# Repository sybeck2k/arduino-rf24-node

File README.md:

# Arduino RF24 Node

@todo

# Credits
Original work credits [@maniacbug][1]

# License

[CC BY-NC-SA][2]

  [1]: http://maniacbug.wordpress.com/
  [2]: http://creativecommons.org/licenses/by-nc-sa/3.0/

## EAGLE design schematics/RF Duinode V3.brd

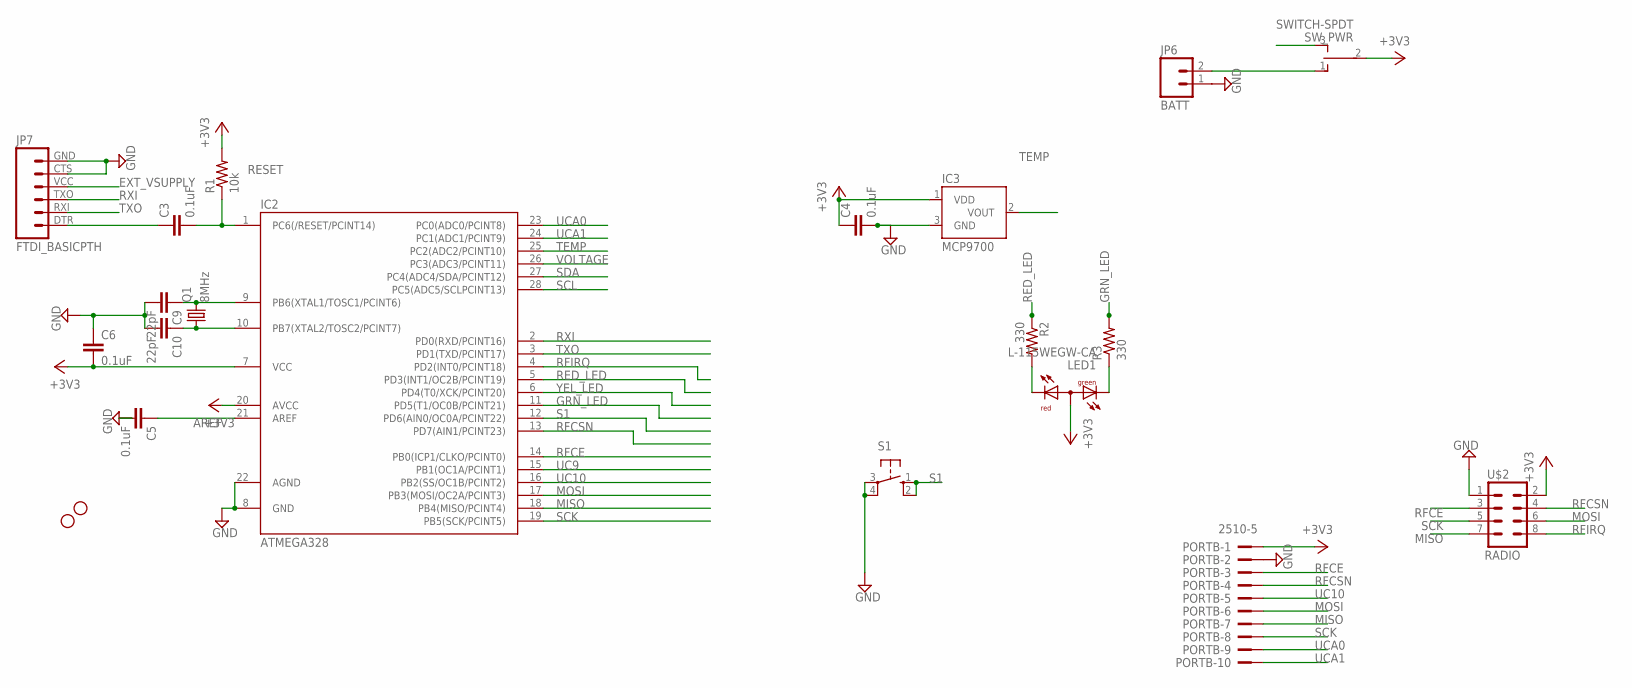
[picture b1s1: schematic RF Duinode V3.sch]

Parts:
C3, C4, C5, C6: 0.1uF; C025-025X050
C9, C10: 22pF; C025-025X050
IC2: ATMEGA328; DIL28-3
IC3: MCP9700; TO-92
JP2, JP8: STAND-OFF
JP6: BATT; 1X02_LOCK
JP7: FTDI_BASICPTH; FTDI_BASIC
LED1: L-115WEGW-CA; DUOLED-A-3MM
PORTB: 2510-5; PAK100/2500-5-10
Q1: 8MHz; HC49/S
R1: 10k; 0204V
R2, R3: 330; 0204V
S1: 10-XX; B3F-10XX
SW_PWR: SWITCH-SPDT; OS102011MS2QN1
U$2: RADIO; 2X4

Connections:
+3V3: C4.1, C6.2, IC2.7 (VCC), IC2.20 (AVCC), IC3.1 (VDD), LED1.2 (A), PORTB.1, R1.2, SW_PWR.2, U$2.2
AREF: C5.1, IC2.21 (AREF)
BATT: JP6.2, SW_PWR.1 (O)
DTR: C3.1, JP7.DTR (1)
EXT_VSUPPLY: JP7.VCC (4), SW_PWR.3 (S)
GND: C4.2, C5.2, C6.1, C9.2, C10.2, IC2.8 (GND), IC2.22 (AGND), IC3.3 (GND), JP6.1, JP7.CTS (5), JP7.GND (6), PORTB.2, S1.3, S1.4 (P1), U$2.1
GRN_LED: IC2.11 (PD5(T1/OC0B/PCINT21)), R3.2
MISO: IC2.18 (PB4(MISO/PCINT4)), PORTB.7, U$2.7
MOSI: IC2.17 (PB3(MOSI/OC2A/PCINT3)), PORTB.6, U$2.6
unnamed: LED1.3 (CR), R2.2
unnamed: LED1.1 (CG), R3.1
RED_LED: IC2.5 (PD3(INT1/OC2B/PCINT19)), R2.1
RESET: C3.2, IC2.1 (PC6(/RESET/PCINT14)), R1.1
RFCE: IC2.14 (PB0(ICP1/CLKO/PCINT0)), PORTB.3, U$2.3
RFCSN: IC2.13 (PD7(AIN1/PCINT23)), PORTB.4, U$2.4
RFIRQ: IC2.4 (PD2(INT0/PCINT18)), U$2.8
RXI: IC2.2 (PD0(RXD/PCINT16)), JP7.TXO (3)
S1: IC2.12 (PD6(AIN0/OC0A/PCINT22)), S1.1 (S), S1.2 (S1)
SCK: IC2.19 (PB5(SCK/PCINT5)), PORTB.8, U$2.5
SCL: IC2.28 (PC5(ADC5/SCLPCINT13))
SDA: IC2.27 (PC4(ADC4/SDA/PCINT12))
TEMP: IC2.25 (PC2(ADC2/PCINT10)), IC3.2 (VOUT)
TXO: IC2.3 (PD1(TXD/PCINT17)), JP7.RXI (2)
UC9: IC2.15 (PB1(OC1A/PCINT1))
UC10: IC2.16 (PB2(SS/OC1B/PCINT2)), PORTB.5
UCA0: IC2.23 (PC0(ADC0/PCINT8)), PORTB.9
UCA1: IC2.24 (PC1(ADC1/PCINT9)), PORTB.10
VOLTAGE: IC2.26 (PC3(ADC3/PCINT11))
XTAL1: C9.1, IC2.9 (PB6(XTAL1/TOSC1/PCINT6)), Q1.2
XTAL2: C10.1, IC2.10 (PB7(XTAL2/TOSC2/PCINT7)), Q1.1
YEL_LED: IC2.6 (PD4(T0/XCK/PCINT20))

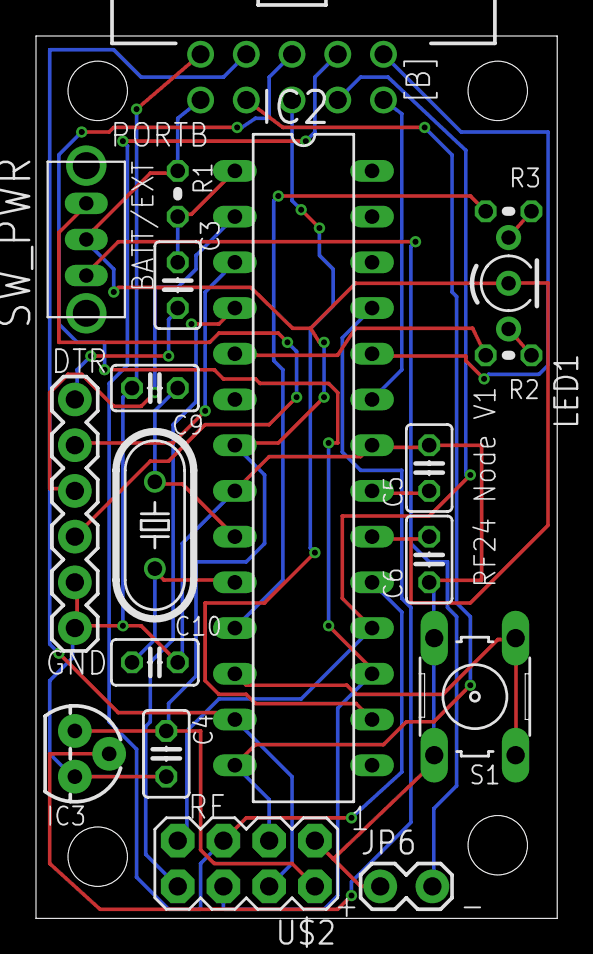
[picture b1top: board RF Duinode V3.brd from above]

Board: 4 copper layers, 29.0 x 49.0 mm, 23 parts (0 on the bottom side), 26 nets.

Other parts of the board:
JP1, JP9: STAND-OFF

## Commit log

2014-01-21 Minor review
2014-01-23 fixed previous commit
2014-01-24 Rotated board by 90deg
2014-01-25 Resized and ready for printing
